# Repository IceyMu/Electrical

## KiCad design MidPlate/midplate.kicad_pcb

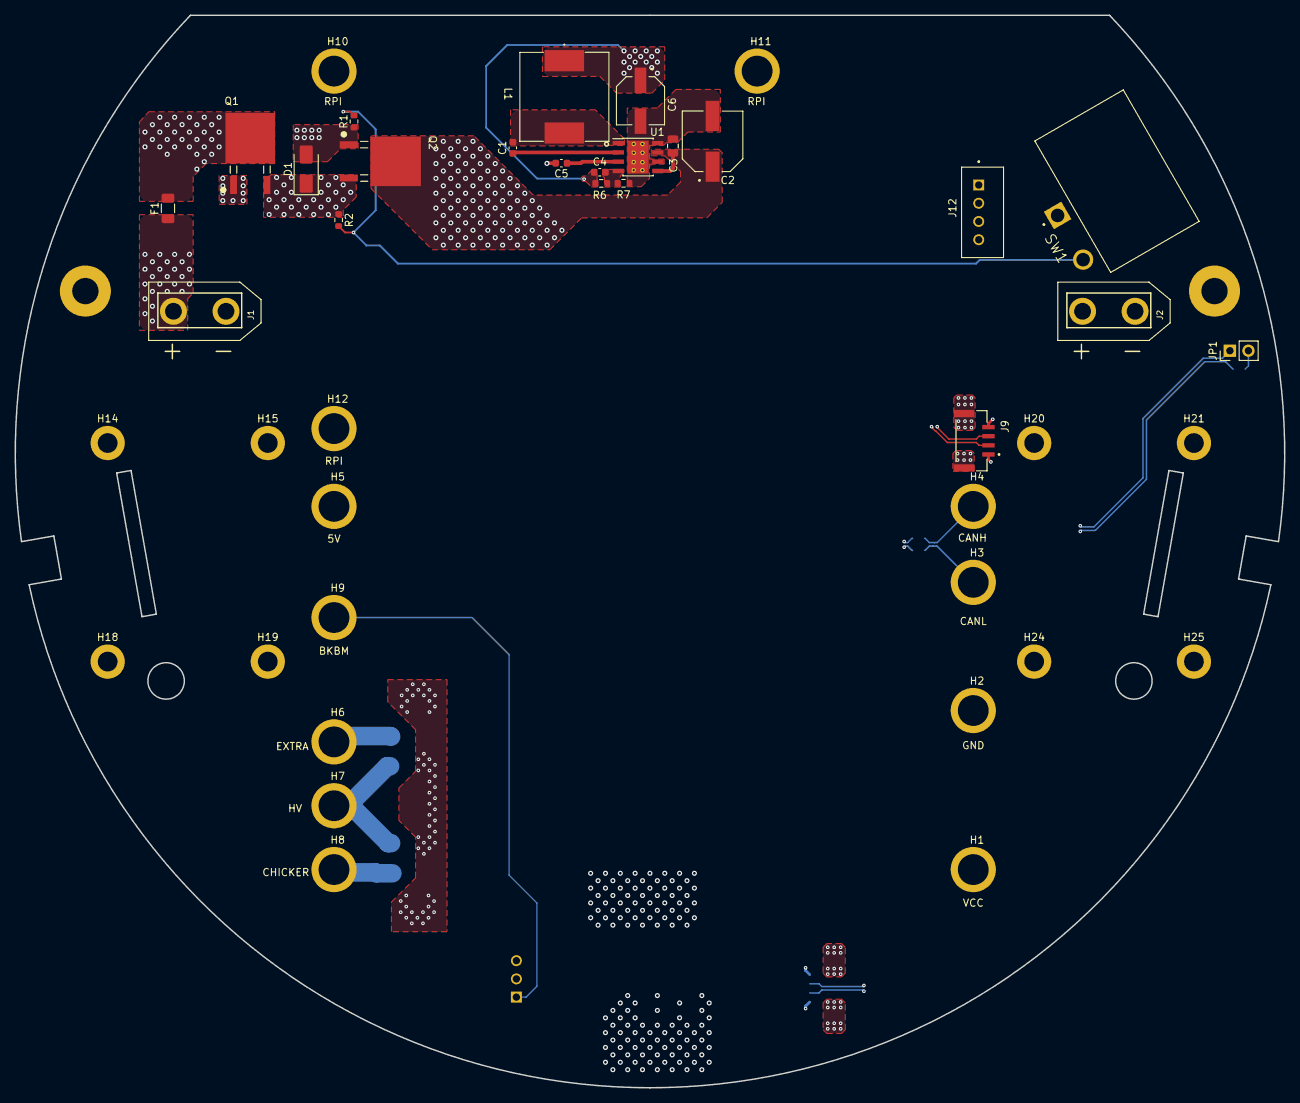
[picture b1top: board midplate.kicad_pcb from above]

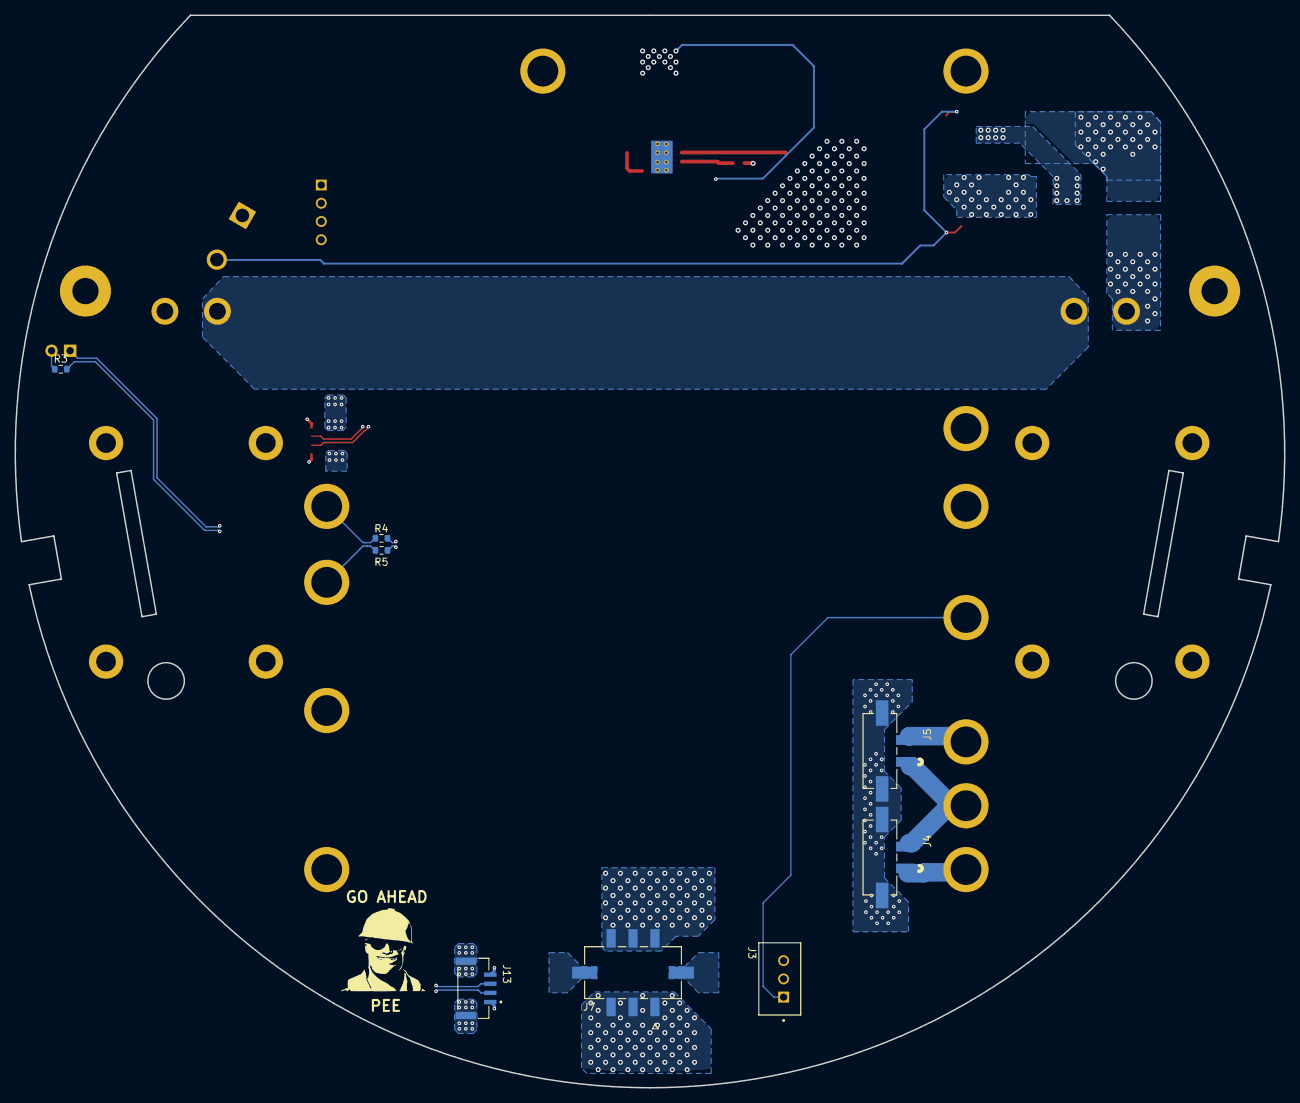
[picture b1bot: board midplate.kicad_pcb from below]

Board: 4 copper layers, 174.0 x 147.0 mm, 52 parts (8 on the bottom side), 23 nets.

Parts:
C1: C_0.1u; C_0603_1608Metric
C2: 25SVPF100M; CAP_25SVPF100M
C3: 10u; C_0805_2012Metric
C4: C_30p; C_0603_1608Metric
C5: 2.2u; C_0603_1608Metric
C6: 16SVPF180M; CAP_16SVPF180M
D1: SMAZ12-13F; D_SMA
F1: 0501015.WR1; Fuse_1206_3216Metric
H1: VCC; SMTSO2515CTJ
H2: GND; SMTSO2515CTJ
H3: CANL; SMTSO2515CTJ
H4: CANH; SMTSO2515CTJ
H5: 5V; SMTSO2515CTJ
H6: EXTRA; SMTSO2515CTJ
H7: HV; SMTSO2515CTJ
H8: CHICKER; SMTSO2515CTJ
H9: BKBM; SMTSO2515CTJ
H10, H11, H12: RPI; SMTSO2515CTJ
H14, H15, H18, H19, H20, H21, H24, H25: MountingHoleM2.5NoThread; MountingHole_2.7mm_M2.5_DIN965_Pad
H47, H48: MountingHoleM2.5NoThread; MountingHole_3.6mm_M3_clearance
J1, J2: XT60; XT60_12-14AWG_POWER
J3: JST_B3B-XH-A
J4, J5: TE_2-1445053-2_2PIN
J7: 1586842-6; TE_1586842-6_6PIN
J9, J13: JST_BM04B-GHS-TBT
J12: JST_B4B-XH-A
JP1: Jumper_2_Bridged; PinHeader_1x02_P2.54mm_Vertical
L1: CDRH127/LDNP-220MC; IND_CDRH127_LDNP-470MC_SUM
Q1, Q2: MCU60P04-TP; DPAK-3_ONS
R1, R2: R_100k; R_0603_1608Metric
R3: R_110R; R_0603_1608Metric
R4, R5: R_0OHM_JUMPER; R_0603_1608Metric
R6: 88.7k; R_0603_1608Metric
R7: 22.1k; R_0603_1608Metric
SW1: RA1H1C112R; SW_RA1H1C112R
U1: LMR23630AFDDAR; TI_SO-PowerPAD-8_ThermalVias

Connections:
+5V: C4.1, C6.1, H5.1, J3.2, J12.1, L1.1, R6.1
/Power Board Connections/CANR+: H4.1, R4.2
/Power Board Connections/CANR-: H3.1, R5.1
/Power Board Connections/MP: J4.MP, J5.MP
/Power Input/BAT_MID: J1.1, J2.2
/Power Input/BOOT: C1.1, U1.2 (BOOT)
/Power Input/FB: C4.2, R6.2, R7.1, U1.4 (FB)
/Power Input/FUSE_VCC: F1.2, Q1.2 (D)
/Power Input/LM_OUT: C1.2, L1.2, U1.1 (SW)
/Power Input/SW: R1.2, R2.2, SW1.2
/Power Input/U1_VCC: C5.1, U1.3 (VCC)
/Power Input/VBAT: F1.1, J1.2
/Power Input/VCC_MID: D1.1 (K), Q1.3 (S), Q2.3 (S), R2.1
/Power Input/VGATE: D1.2 (A), Q1.1 (G), Q2.1 (G), R1.1
BKBM: H9.1, J3.1
CAN+: J9.3, J12.4, J13.2, JP1.1 (A), R4.1
CAN-: J9.2, J12.3, J13.3, R3.2, R5.2
CHICKER: H8.1, J4.1
EXTRA: H6.1, J5.2
GND: C2.2, C3.2, C5.2, C6.2, H2.1, J2.1, J3.3, J7.1, J7.2, J7.3, J9.1, J9.4, J12.2, J13.1, J13.4, R7.2, SW1.1, U1.6 (AGND), U1.8 (PGND), U1.9 (PAD)
HV: H7.1, J4.2, J5.1
unnamed: JP1.2 (B), R3.1
VCC: C2.1, C3.1, H1.1, J7.4, J7.5, J7.6, Q2.2 (D), U1.5 (EN/SYNC), U1.7 (VIN)

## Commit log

2024-03-11 update motor mount footprints
